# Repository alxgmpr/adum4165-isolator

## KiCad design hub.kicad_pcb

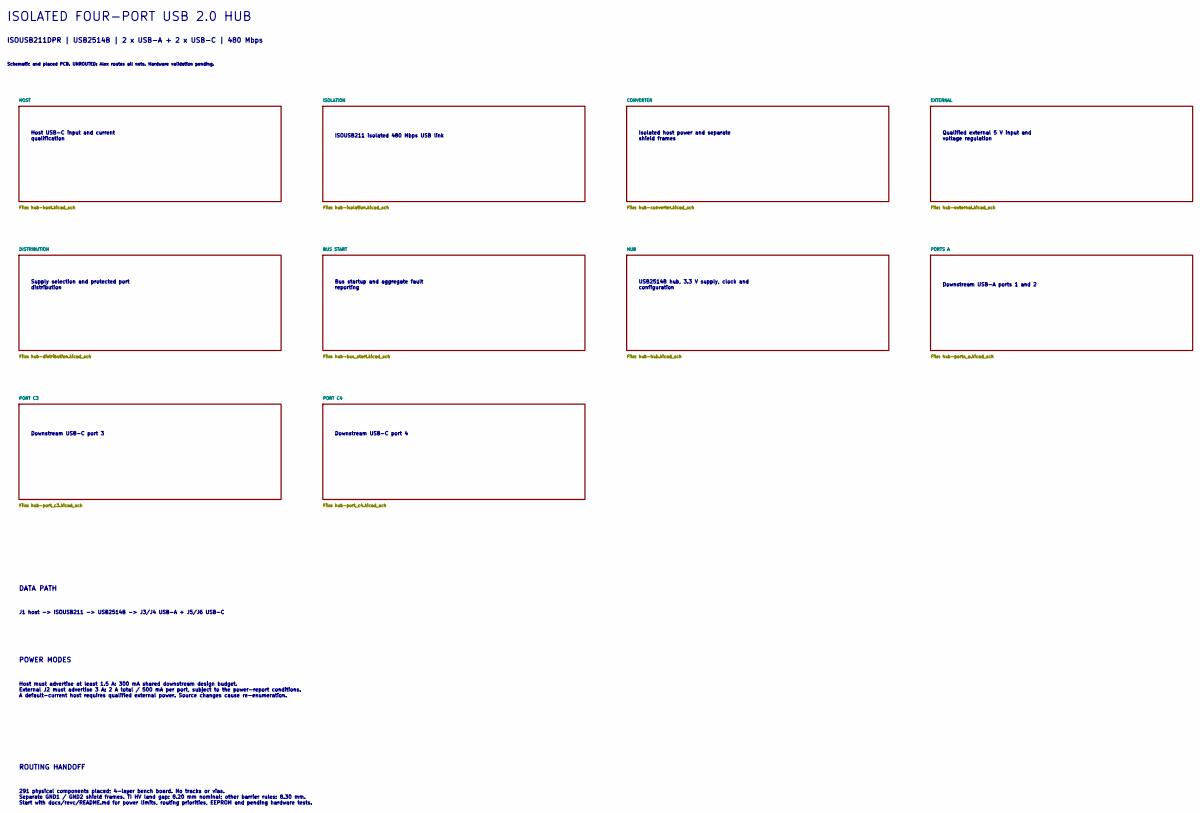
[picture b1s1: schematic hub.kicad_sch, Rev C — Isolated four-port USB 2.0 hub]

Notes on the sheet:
ISOLATED FOUR-PORT USB 2.0 HUB
ISOUSB211DPR | USB2514B | 2 x USB-A + 2 x USB-C | 480 Mbps
Schematic and placed PCB. UNROUTED: Alex routes all nets. Hardware validation pending.
Host USB-C input and current qualification
ISOUSB211 isolated 480 Mbps USB link
Isolated host power and separate shield frames
Qualified external 5 V input and voltage regulation
Supply selection and protected port distribution
Bus startup and aggregate fault reporting
USB2514B hub, 3.3 V supply, clock and configuration
Downstream USB-A ports 1 and 2
Downstream USB-C port 3
Downstream USB-C port 4
DATA PATH
J1 host -> ISOUSB211 -> USB2514B -> J3/J4 USB-A + J5/J6 USB-C
POWER MODES
Host must advertise at least 1.5 A: 300 mA shared downstream design budget. External J2 must advertise 3 A: 2 A total / 500 mA per port, subject to the power-report conditions. A default-current host requires qualified external power. Source changes cause re-enumeration.
ROUTING HANDOFF
291 physical components placed; 4-layer bench board. No tracks or vias. Separate GND1 / GND2 shield frames. TI HV land gap: 8.20 mm nominal; other barrier rules: 8.30 mm. Start with docs/revc/README.md for power limits, routing priorities, EEPROM and pending hardware tests.

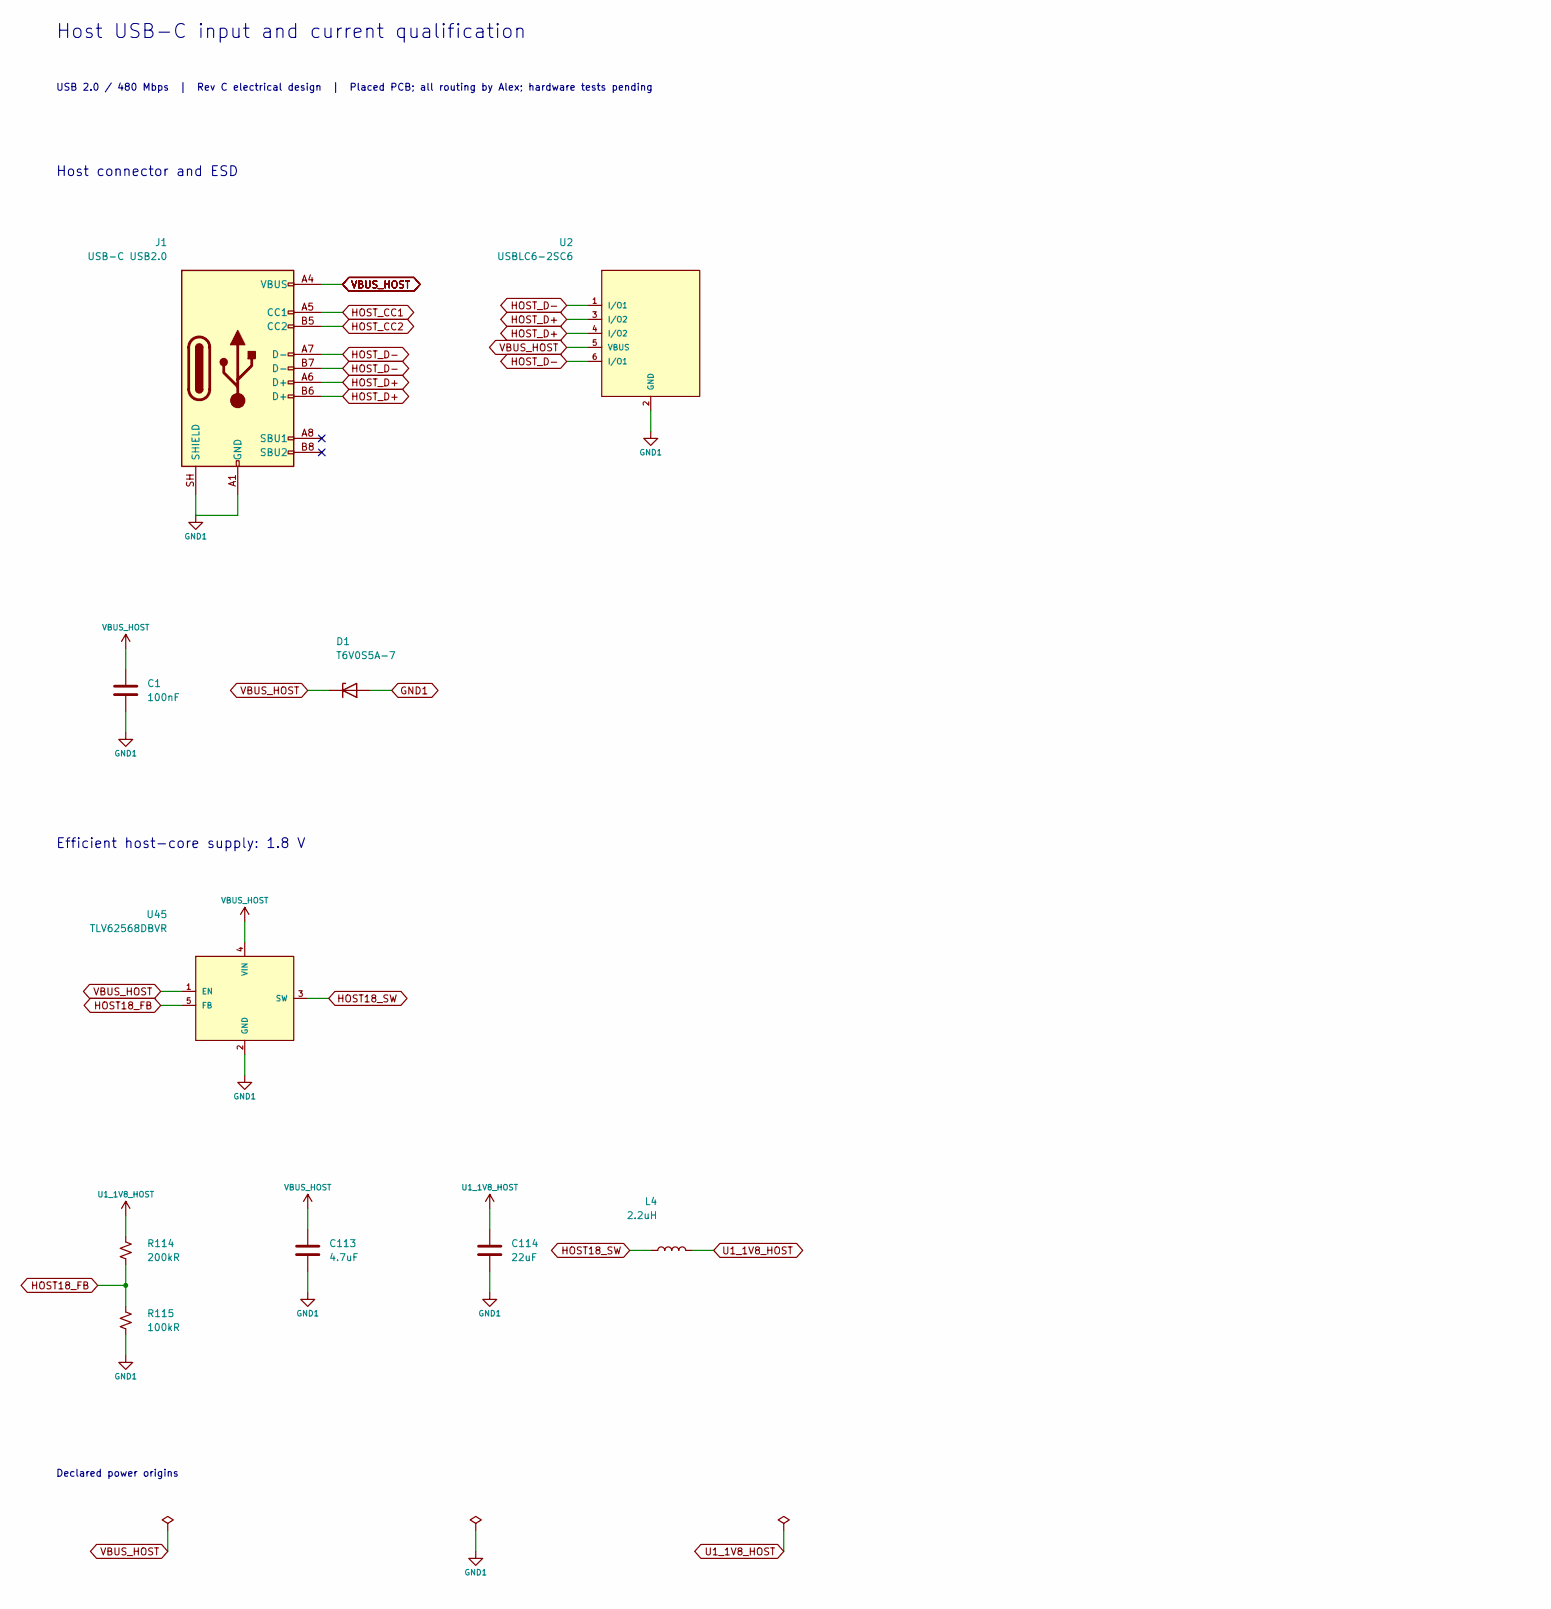
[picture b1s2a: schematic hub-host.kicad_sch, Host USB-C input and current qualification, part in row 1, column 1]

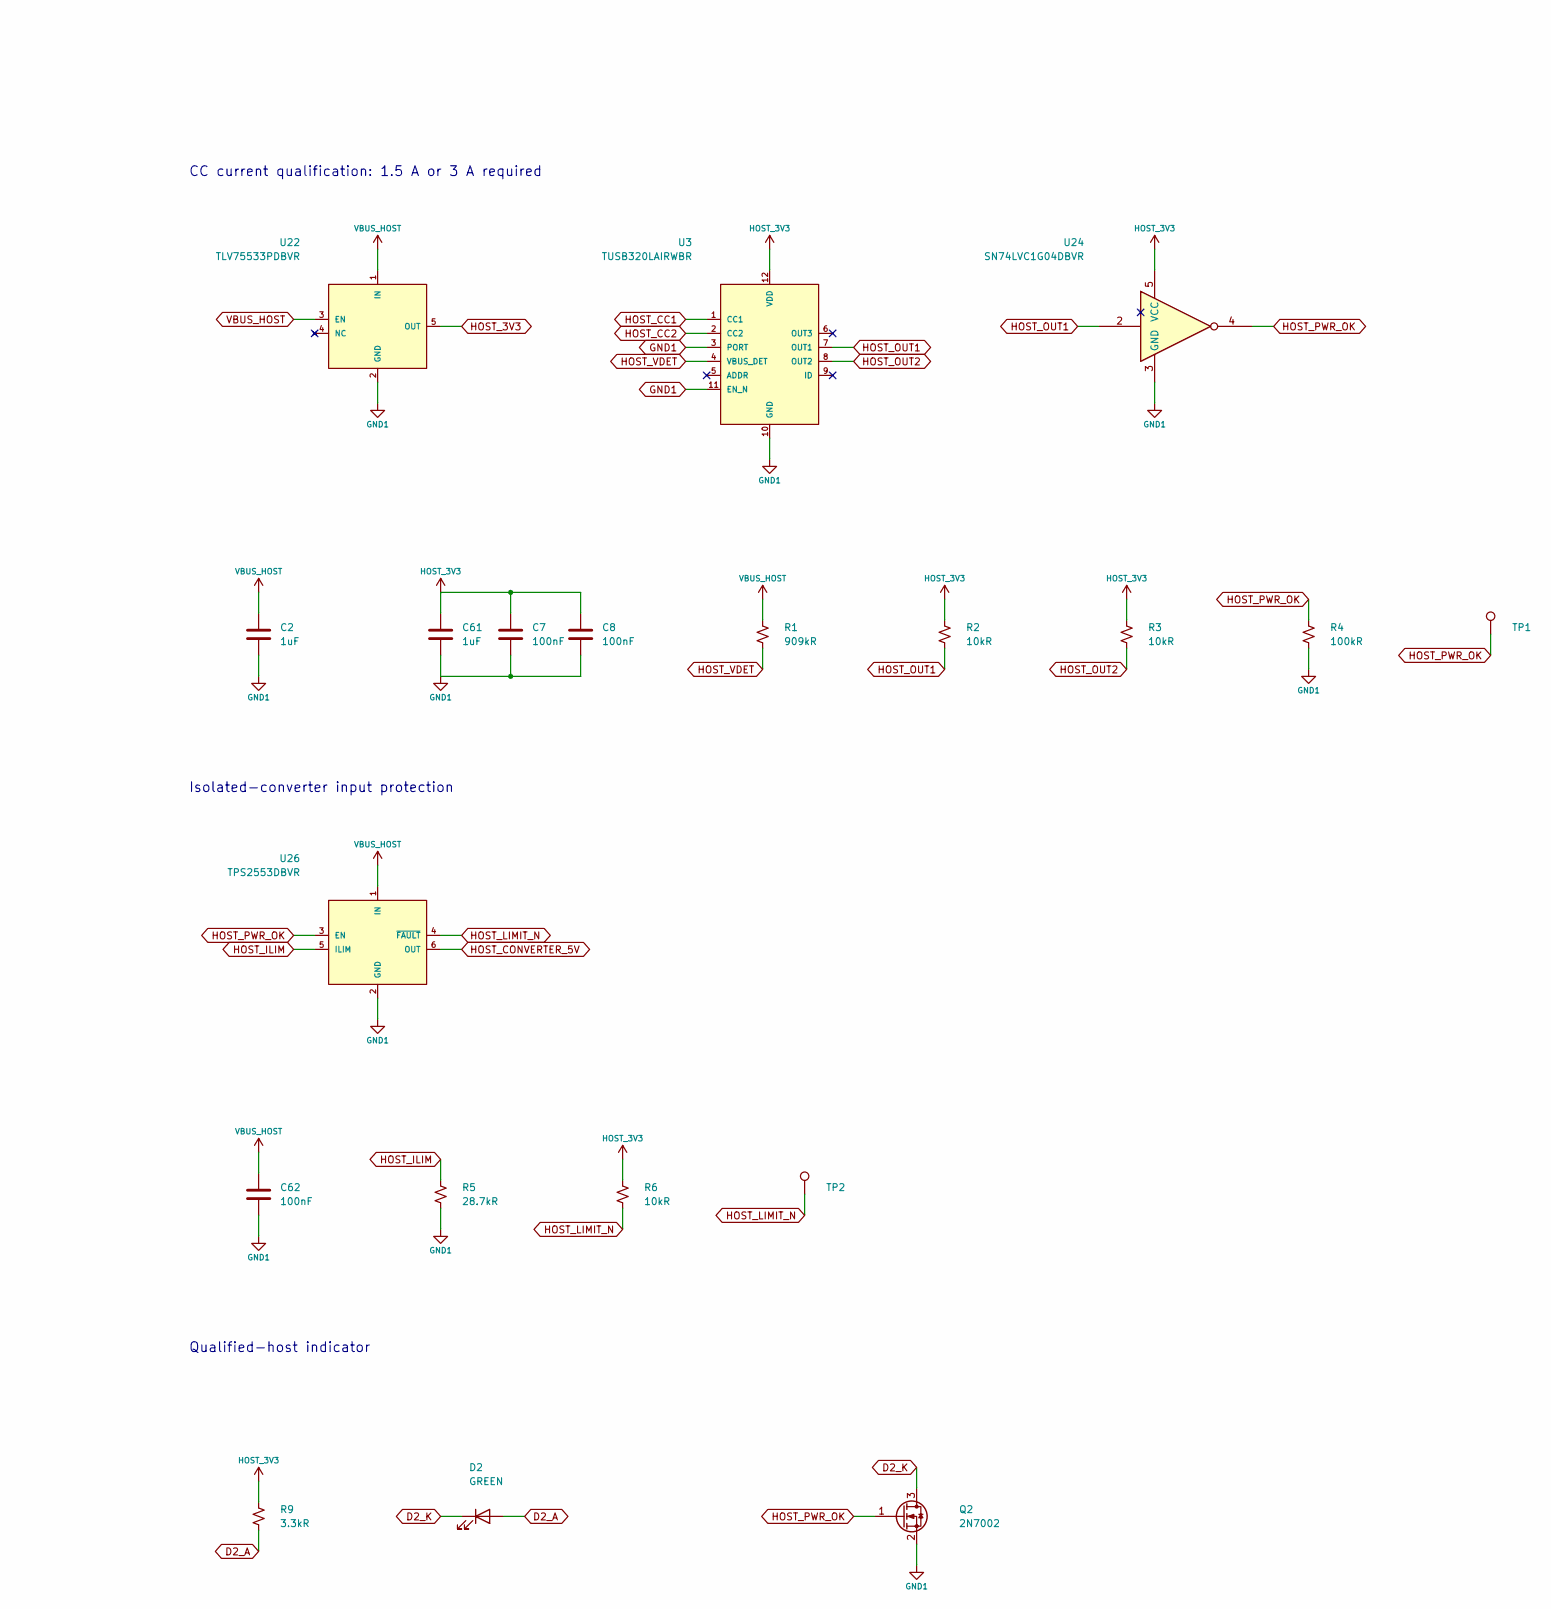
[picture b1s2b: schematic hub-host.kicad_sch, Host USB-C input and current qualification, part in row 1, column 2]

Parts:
C1, C7, C8, C62: 100nF; C_0402_1005Metric; Ratings 50V X7R 10%; MPN GRM155R71H104KE14D; LCSC C77020
C2, C61: 1uF; C_0603_1608Metric; Ratings 25V X5R 10%; MPN GRM188R61E105KA12D; LCSC C77046
C113: 4.7uF; C_0805_2012Metric; Ratings 25V X5R 10%; MPN GRM21BR61E475KA12L; LCSC C77077
C114: 22uF; C_1210_3225Metric; Ratings 25V X7R 10%; MPN GRM32ER71E226KE15L; LCSC C21397
D1: T6V0S5A-7; D_SOD-523; Ratings See exact manufacturer datasheet; MPN T6V0S5A-7; LCSC C19950551
D2: GREEN; LED_0603_1608Metric; Ratings See exact manufacturer datasheet; MPN LTST-C190KGKT; LCSC C125094
J1: USB-C USB2.0; USB_C_Receptacle_HRO_TYPE-C-31-M-12; Ratings See exact manufacturer datasheet; MPN TYPE-C-31-M-12; LCSC C165948
L4: 2.2uH; Coilcraft_XFL4020_4x4mm; Ratings See exact manufacturer datasheet; MPN XFL4020-222MEC; LCSC C122469
Q2: 2N7002; SOT-23; Ratings See exact manufacturer datasheet; MPN 2N7002,215; LCSC C65189
R1: 909kR; R_0402_1005Metric; Ratings 1%, 0.1W, 50V; MPN ERJ2RKF9093X; LCSC C2085054
R2, R3, R6: 10kR; R_0402_1005Metric; Ratings 1%, 0.1W, 50V; MPN ERJ2RKF1002X; LCSC C191123
R4, R115: 100kR; R_0402_1005Metric; Ratings 1%, 0.1W, 50V; MPN ERJ2RKF1003X; LCSC C192169
R5: 28.7kR; R_0402_1005Metric; Ratings 1%, 0.1W, 50V; MPN ERJ2RKF2872X
R9: 3.3kR; R_0402_1005Metric; Ratings 1%, 0.1W, 50V; MPN ERJ2RKF3301X; LCSC C409909
R114: 200kR; R_0402_1005Metric; Ratings 1%, 0.1W, 50V; MPN ERJ2RKF2003X; LCSC C413111
TP1: HOST_PWR_OK; TestPoint_Pad_D1.0mm; Ratings Exposed test pad; no purchased part
TP2: HOST_LIMIT_N; TestPoint_Pad_D1.0mm; Ratings Exposed test pad; no purchased part
U2: USBLC6-2SC6; SOT-23-6; Ratings See exact manufacturer datasheet; MPN USBLC6-2SC6; LCSC C7519
U3: TUSB320LAIRWBR; Texas_X2QFN-12_1.6x1.6mm_P0.4mm; Ratings See exact manufacturer datasheet; MPN TUSB320LAIRWBR; LCSC C132554
U22: TLV75533PDBVR; SOT-23-5; Ratings See exact manufacturer datasheet; MPN TLV75533PDBVR; LCSC C404027
U24: SN74LVC1G04DBVR; SOT-23-5; Ratings See exact manufacturer datasheet; MPN SN74LVC1G04DBVR; LCSC C7827
U26: TPS2553DBVR; SOT-23-6; Ratings See exact manufacturer datasheet; MPN TPS2553DBVR; LCSC C55266
U45: TLV62568DBVR; SOT-23-5; Ratings See exact manufacturer datasheet; MPN TLV62568DBVR; LCSC C163219

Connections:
D2_A: D2.2 (A), R9.2
D2_K: D2.1 (K), Q2.3 (D)
GND1: C1.2, C2.2, C7.2, C8.2, C61.2, C62.2, C113.2, C114.2, D1.2 (A), J1.A1 (GND), J1.A12 (GND), J1.B1 (GND), J1.B12 (GND), J1.SH (SHIELD), Q2.2 (S), R4.2, R5.2, R115.2, U2.2 (GND), U3.3 (PORT), U3.10 (GND), U3.11 (EN_N), U22.2 (GND), U24.3 (GND), U26.2 (GND), U45.2 (GND); also elsewhere on the board
HOST18_FB: R114.2, R115.1, U45.5 (FB)
HOST18_SW: L4.1, U45.3 (SW)
HOST_3V3: C7.1, C8.1, C61.1, R2.1, R3.1, R6.1, R9.1, U3.12 (VDD), U22.5 (OUT), U24.5 (VCC)
HOST_CC1: J1.A5 (CC1), U3.1 (CC1)
HOST_CC2: J1.B5 (CC2), U3.2 (CC2)
HOST_CONVERTER_5V: U26.6 (OUT); also elsewhere on the board
HOST_D+: J1.A6 (D+), J1.B6 (D+), U2.3 (I/O2), U2.4 (I/O2); also elsewhere on the board
HOST_D-: J1.A7 (D-), J1.B7 (D-), U2.1 (I/O1), U2.6 (I/O1); also elsewhere on the board
HOST_ILIM: R5.1, U26.5 (ILIM)
HOST_LIMIT_N: R6.2, TP2.1, U26.4 (~FAULT)
HOST_OUT1: R2.2, U3.7 (OUT1), U24.2
HOST_OUT2: R3.2, U3.8 (OUT2)
HOST_PWR_OK: Q2.1 (G), R4.1, TP1.1, U24.4, U26.3 (EN)
HOST_VDET: R1.2, U3.4 (VBUS_DET)
U1_1V8_HOST: C114.1, L4.2, R114.1; also elsewhere on the board
VBUS_HOST: C1.1, C2.1, C62.1, C113.1, D1.1 (K), J1.A4 (VBUS), J1.A9 (VBUS), J1.B4 (VBUS), J1.B9 (VBUS), R1.1, U2.5 (VBUS), U22.1 (IN), U22.3 (EN), U26.1 (IN), U45.1 (EN), U45.4 (VIN); also elsewhere on the board

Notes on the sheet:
Host USB-C input and current qualification
USB 2.0 / 480 Mbps | Rev C electrical design | Placed PCB; all routing by Alex; hardware tests pending
Host connector and ESD
CC current qualification: 1.5 A or 3 A required
Isolated-converter input protection
Efficient host-core supply: 1.8 V
Qualified-host indicator
Declared power origins

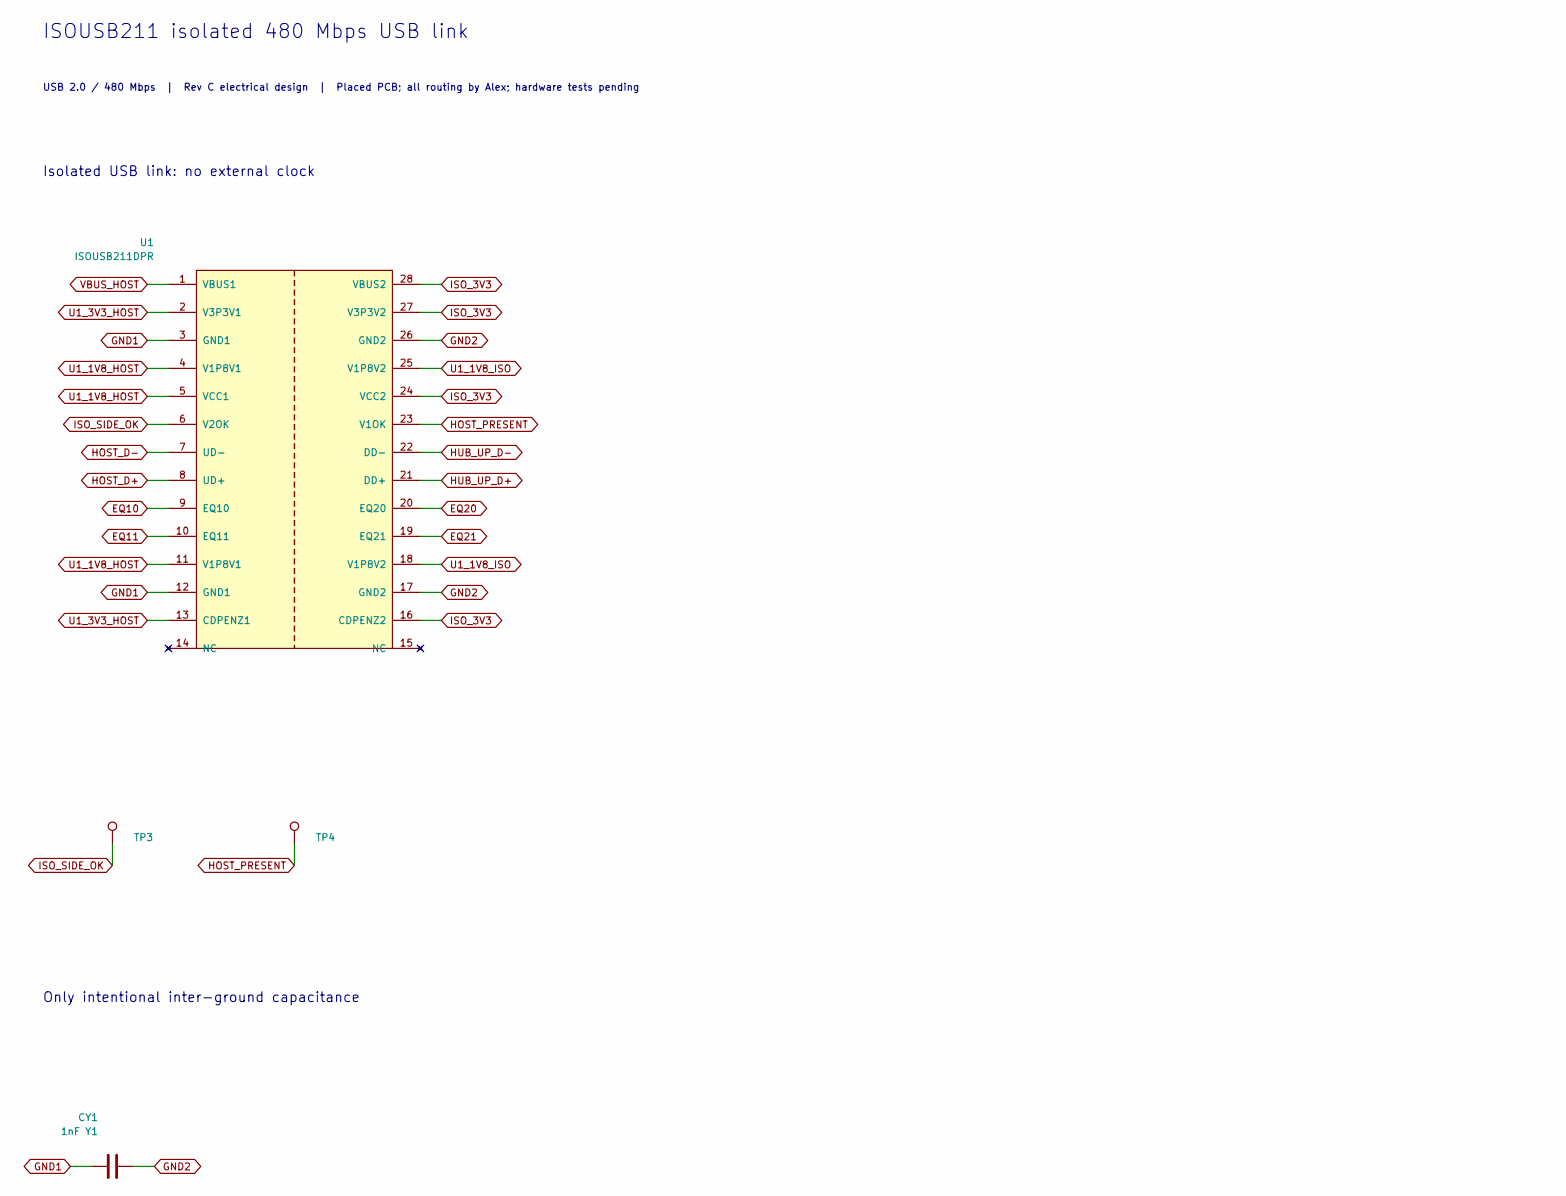
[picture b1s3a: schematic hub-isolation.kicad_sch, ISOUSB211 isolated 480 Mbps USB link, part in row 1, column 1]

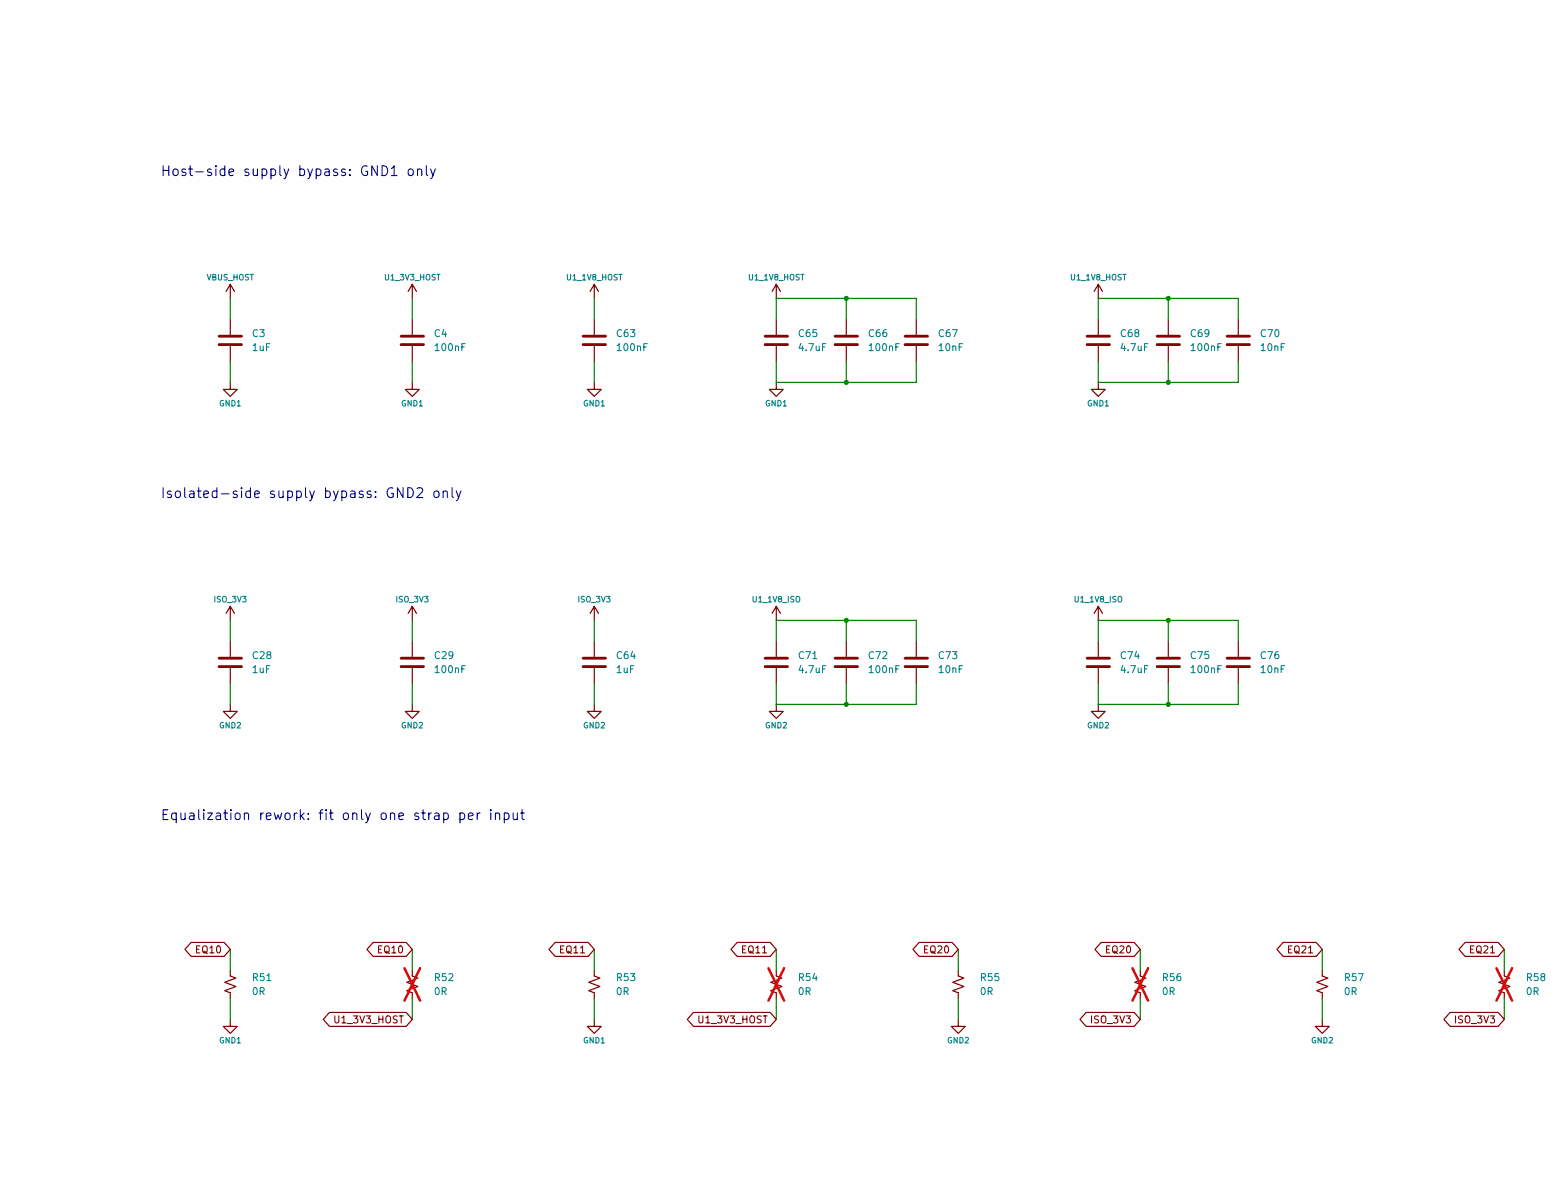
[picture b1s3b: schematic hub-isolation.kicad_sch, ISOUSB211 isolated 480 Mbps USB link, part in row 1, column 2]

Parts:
C3, C28, C64: 1uF; C_0603_1608Metric; Ratings 25V X5R 10%; MPN GRM188R61E105KA12D; LCSC C77046
C4, C29, C63, C66, C69, C72, C75: 100nF; C_0402_1005Metric; Ratings 50V X7R 10%; MPN GRM155R71H104KE14D; LCSC C77020
C65, C68, C71, C74: 4.7uF; C_0603_1608Metric; Ratings 25V X5R 10%; MPN GRM188R61E475KE11D; LCSC C90057
C67, C70, C73, C76: 10nF; C_0402_1005Metric; Ratings 50V X7R 10%; MPN GRM155R71H103KA88D; LCSC C77019
CY1: 1nF Y1; C_Disc_D7.0mm_W5.5mm_P14.00mm; Ratings See exact manufacturer datasheet; MPN Q07F3Z102MA5B0S0N0; LCSC C2914611
R51, R53, R55, R57: 0R; R_0402_1005Metric; Ratings 0R jumper, 0402, 1A rated current; MPN ERJ2GE0R00X; LCSC C242160
R52, R54, R56, R58: 0R; R_0402_1005Metric; Ratings 0R jumper, 0402, 1A rated current; MPN ERJ2GE0R00X; LCSC C242160; not fitted
TP3: ISO_SIDE_OK; TestPoint_Pad_D1.0mm; Ratings Exposed test pad; no purchased part
TP4: HOST_PRESENT; TestPoint_Pad_D1.0mm; Ratings Exposed test pad; no purchased part
U1: ISOUSB211DPR; TI_DP0028A-C02_HV_SSOP28_8.2mm_Clearance; Ratings See exact manufacturer datasheet; MPN ISOUSB211DPR; LCSC C5772877

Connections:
EQ10: R51.1, R52.1, U1.9 (EQ10)
EQ11: R53.1, R54.1, U1.10 (EQ11)
EQ20: R55.1, R56.1, U1.20 (EQ20)
EQ21: R57.1, R58.1, U1.19 (EQ21)
GND1: C3.2, C4.2, C63.2, C65.2, C66.2, C67.2, C68.2, C69.2, C70.2, CY1.1, R51.2, R53.2, U1.3 (GND1), U1.12 (GND1); also elsewhere on the board
GND2: C28.2, C29.2, C64.2, C71.2, C72.2, C73.2, C74.2, C75.2, C76.2, CY1.2, R55.2, R57.2, U1.17 (GND2), U1.26 (GND2); also elsewhere on the board
HOST_D+: U1.8 (UD+); also elsewhere on the board
HOST_D-: U1.7 (UD-); also elsewhere on the board
HOST_PRESENT: TP4.1, U1.23 (V1OK); also elsewhere on the board
HUB_UP_D+: U1.21 (DD+); also elsewhere on the board
HUB_UP_D-: U1.22 (DD-); also elsewhere on the board
ISO_3V3: C28.1, C29.1, C64.1, R56.2, R58.2, U1.16 (CDPENZ2), U1.24 (VCC2), U1.27 (V3P3V2), U1.28 (VBUS2); also elsewhere on the board
ISO_SIDE_OK: TP3.1, U1.6 (V2OK)
U1_1V8_HOST: C63.1, C65.1, C66.1, C67.1, C68.1, C69.1, C70.1, U1.4 (V1P8V1), U1.5 (VCC1), U1.11 (V1P8V1); also elsewhere on the board
U1_1V8_ISO: C71.1, C72.1, C73.1, C74.1, C75.1, C76.1, U1.18 (V1P8V2), U1.25 (V1P8V2)
U1_3V3_HOST: C4.1, R52.2, R54.2, U1.2 (V3P3V1), U1.13 (CDPENZ1)
VBUS_HOST: C3.1, U1.1 (VBUS1); also elsewhere on the board

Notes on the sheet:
ISOUSB211 isolated 480 Mbps USB link
USB 2.0 / 480 Mbps | Rev C electrical design | Placed PCB; all routing by Alex; hardware tests pending
Isolated USB link: no external clock
Host-side supply bypass: GND1 only
Isolated-side supply bypass: GND2 only
Equalization rework: fit only one strap per input
Only intentional inter-ground capacitance

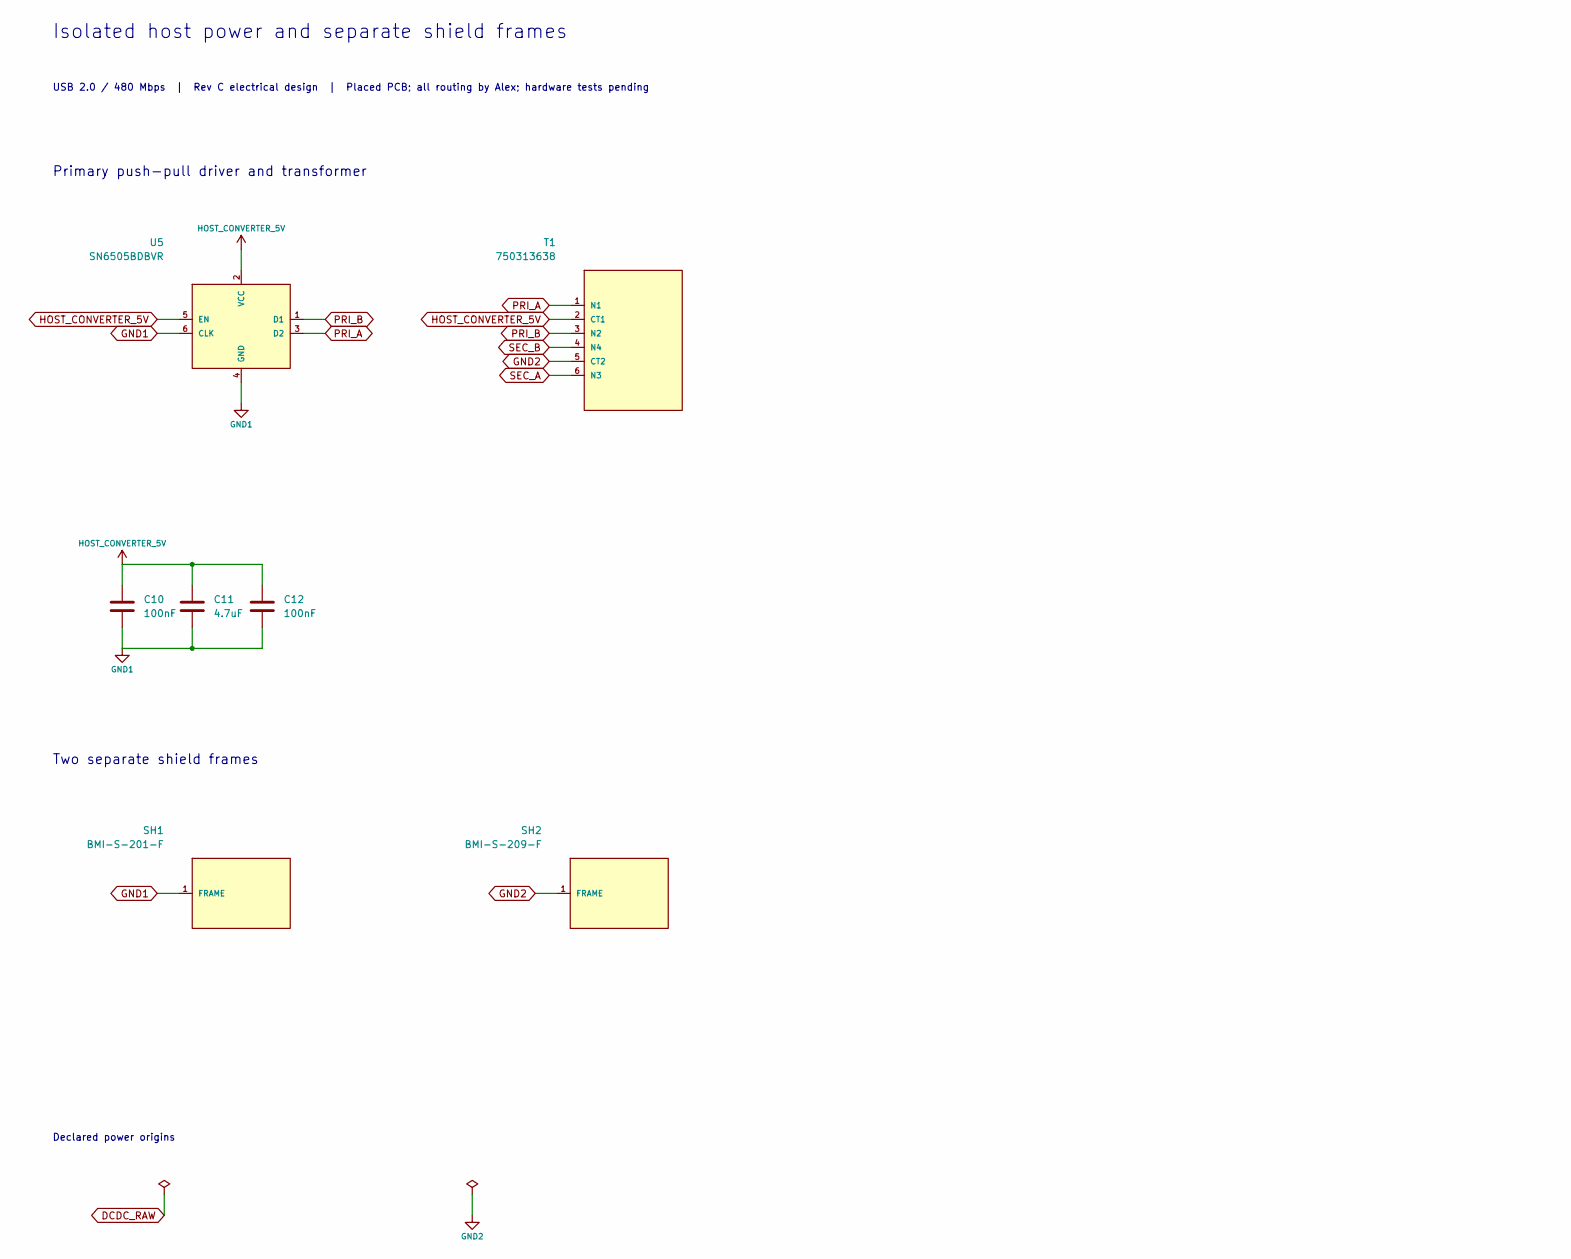
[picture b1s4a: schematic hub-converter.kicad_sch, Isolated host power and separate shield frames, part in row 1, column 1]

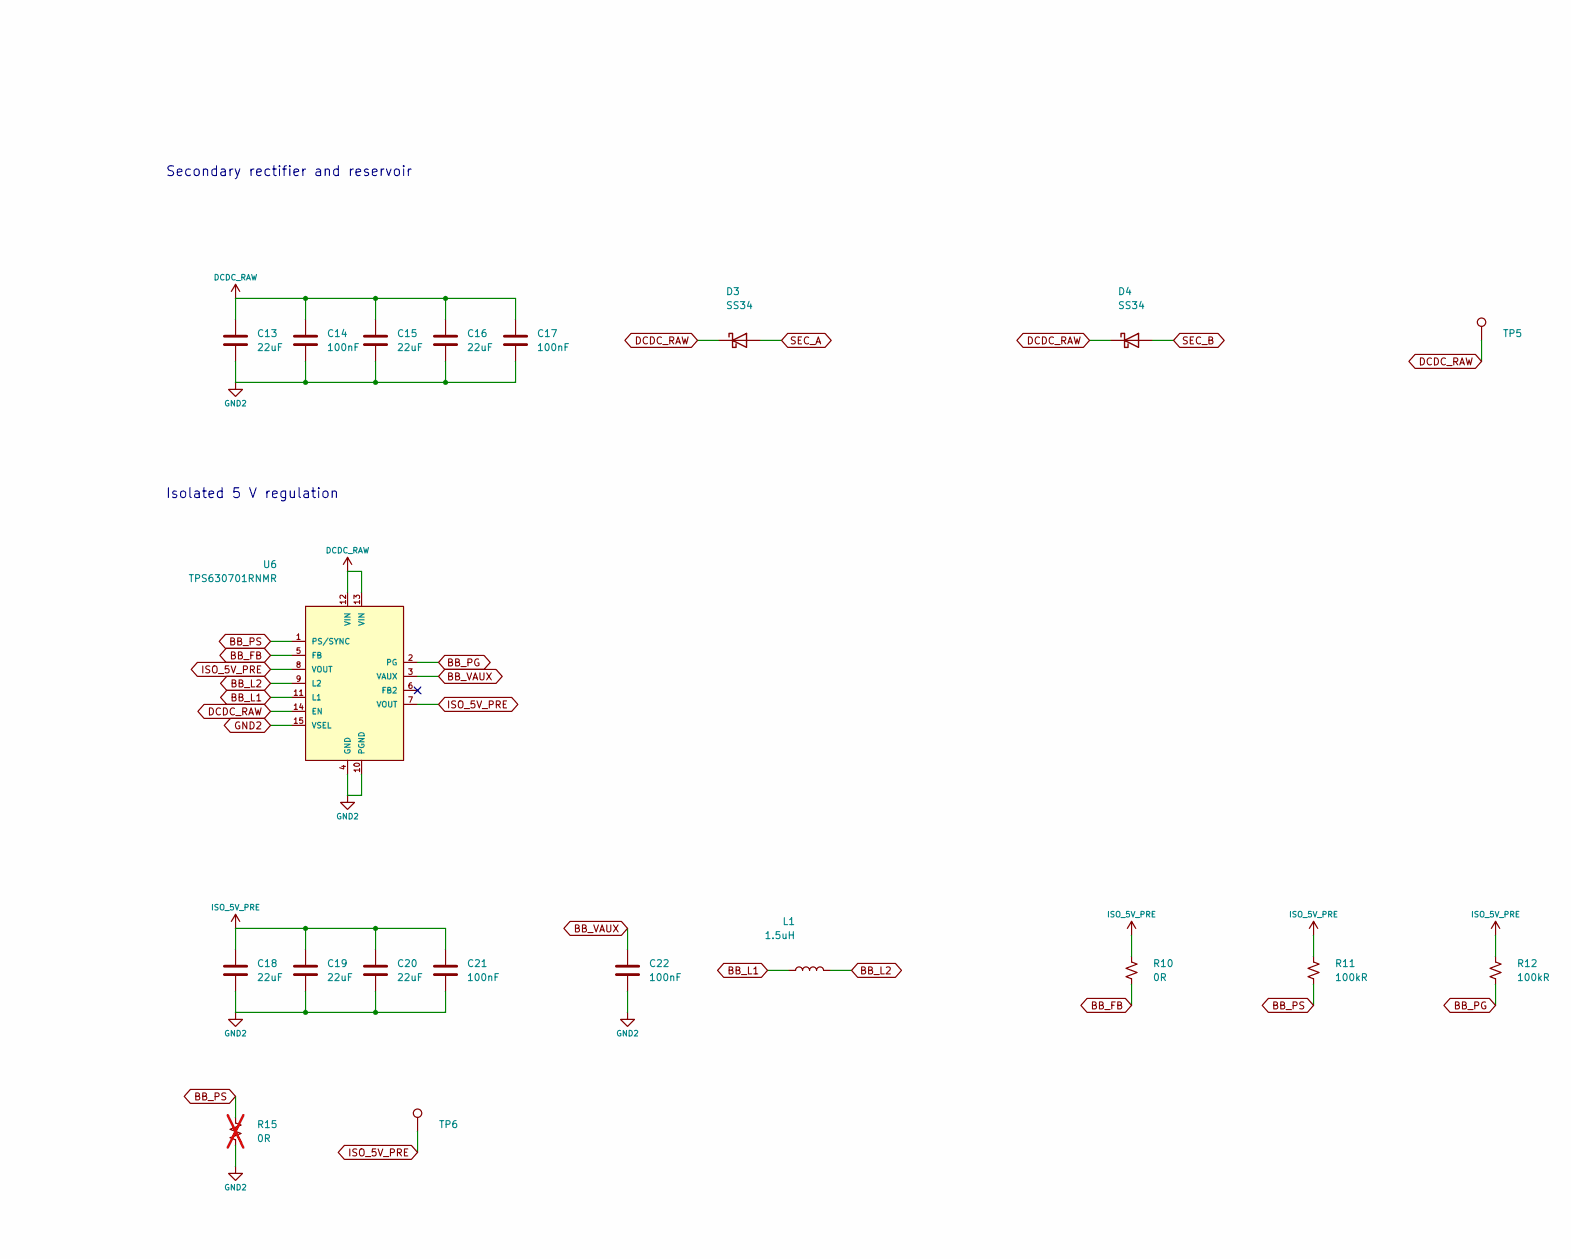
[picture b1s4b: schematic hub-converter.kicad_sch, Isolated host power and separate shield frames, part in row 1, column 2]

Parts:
C10, C12, C14, C17, C21, C22: 100nF; C_0402_1005Metric; Ratings 50V X7R 10%; MPN GRM155R71H104KE14D; LCSC C77020
C11: 4.7uF; C_0603_1608Metric; Ratings 25V X5R 10%; MPN GRM188R61E475KE11D; LCSC C90057
C13, C15, C16, C18, C19, C20: 22uF; C_1210_3225Metric; Ratings 25V X7R 10%; MPN GRM32ER71E226KE15L; LCSC C21397
D3, D4: SS34; D_SMA; Ratings See exact manufacturer datasheet; MPN SS34; LCSC C8678
L1: 1.5uH; Coilcraft_XFL4020_4x4mm; Ratings See exact manufacturer datasheet; MPN XFL4020-152MEC; LCSC C3033018
R10: 0R; R_0402_1005Metric; Ratings 0R jumper, 0402, 1A rated current; MPN ERJ2GE0R00X; LCSC C242160
R11, R12: 100kR; R_0402_1005Metric; Ratings 1%, 0.1W, 50V; MPN ERJ2RKF1003X; LCSC C192169
R15: 0R; R_0402_1005Metric; Ratings 0R jumper, 0402, 1A rated current; MPN ERJ2GE0R00X; LCSC C242160; not fitted
SH1: BMI-S-201-F; Laird_Technologies_BMI-S-201-F_13.66x12.70mm; Ratings Separate grounded frame; removable BMI-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; MPN BMI-S-201-F
SH2: BMI-S-209-F; Laird_Technologies_BMI-S-209-F_29.36x18.50mm; Ratings Separate grounded frame; removable BMI-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; MPN BMI-S-209-F
T1: 750313638; WE_750313638; Ratings See exact manufacturer datasheet; MPN 750313638
TP5: DCDC_RAW; TestPoint_Pad_D1.0mm; Ratings Exposed test pad; no purchased part
TP6: ISO_5V_PRE; TestPoint_Pad_D1.0mm; Ratings Exposed test pad; no purchased part
U5: SN6505BDBVR; SOT-23-6; Ratings See exact manufacturer datasheet; MPN SN6505BDBVR; LCSC C74518
U6: TPS630701RNMR; TPS630701RNM_VQFN-HR-15; Ratings See exact manufacturer datasheet; MPN TPS630701RNMR; LCSC C2876599

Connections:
BB_FB: R10.2, U6.5 (FB)
BB_L1: L1.1, U6.11 (L1)
BB_L2: L1.2, U6.9 (L2)
BB_PG: R12.2, U6.2 (PG)
BB_PS: R11.2, R15.1, U6.1 (PS/SYNC)
BB_VAUX: C22.1, U6.3 (VAUX)
DCDC_RAW: C13.1, C14.1, C15.1, C16.1, C17.1, D3.1 (K), D4.1 (K), TP5.1, U6.12 (VIN), U6.13 (VIN), U6.14 (EN)
GND1: C10.2, C11.2, C12.2, SH1.1 (FRAME), U5.4 (GND), U5.6 (CLK); also elsewhere on the board
GND2: C13.2, C14.2, C15.2, C16.2, C17.2, C18.2, C19.2, C20.2, C21.2, C22.2, R15.2, SH2.1 (FRAME), T1.5 (CT2), U6.4 (GND), U6.10 (PGND), U6.15 (VSEL); also elsewhere on the board
HOST_CONVERTER_5V: C10.1, C11.1, C12.1, T1.2 (CT1), U5.2 (VCC), U5.5 (EN); also elsewhere on the board
ISO_5V_PRE: C18.1, C19.1, C20.1, C21.1, R10.1, R11.1, R12.1, TP6.1, U6.7 (VOUT), U6.8 (VOUT); also elsewhere on the board
PRI_A: T1.1 (N1), U5.3 (D2)
PRI_B: T1.3 (N2), U5.1 (D1)
SEC_A: D3.2 (A), T1.6 (N3)
SEC_B: D4.2 (A), T1.4 (N4)

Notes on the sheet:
Isolated host power and separate shield frames
USB 2.0 / 480 Mbps | Rev C electrical design | Placed PCB; all routing by Alex; hardware tests pending
Primary push-pull driver and transformer
Secondary rectifier and reservoir
Isolated 5 V regulation
Two separate shield frames
Declared power origins
